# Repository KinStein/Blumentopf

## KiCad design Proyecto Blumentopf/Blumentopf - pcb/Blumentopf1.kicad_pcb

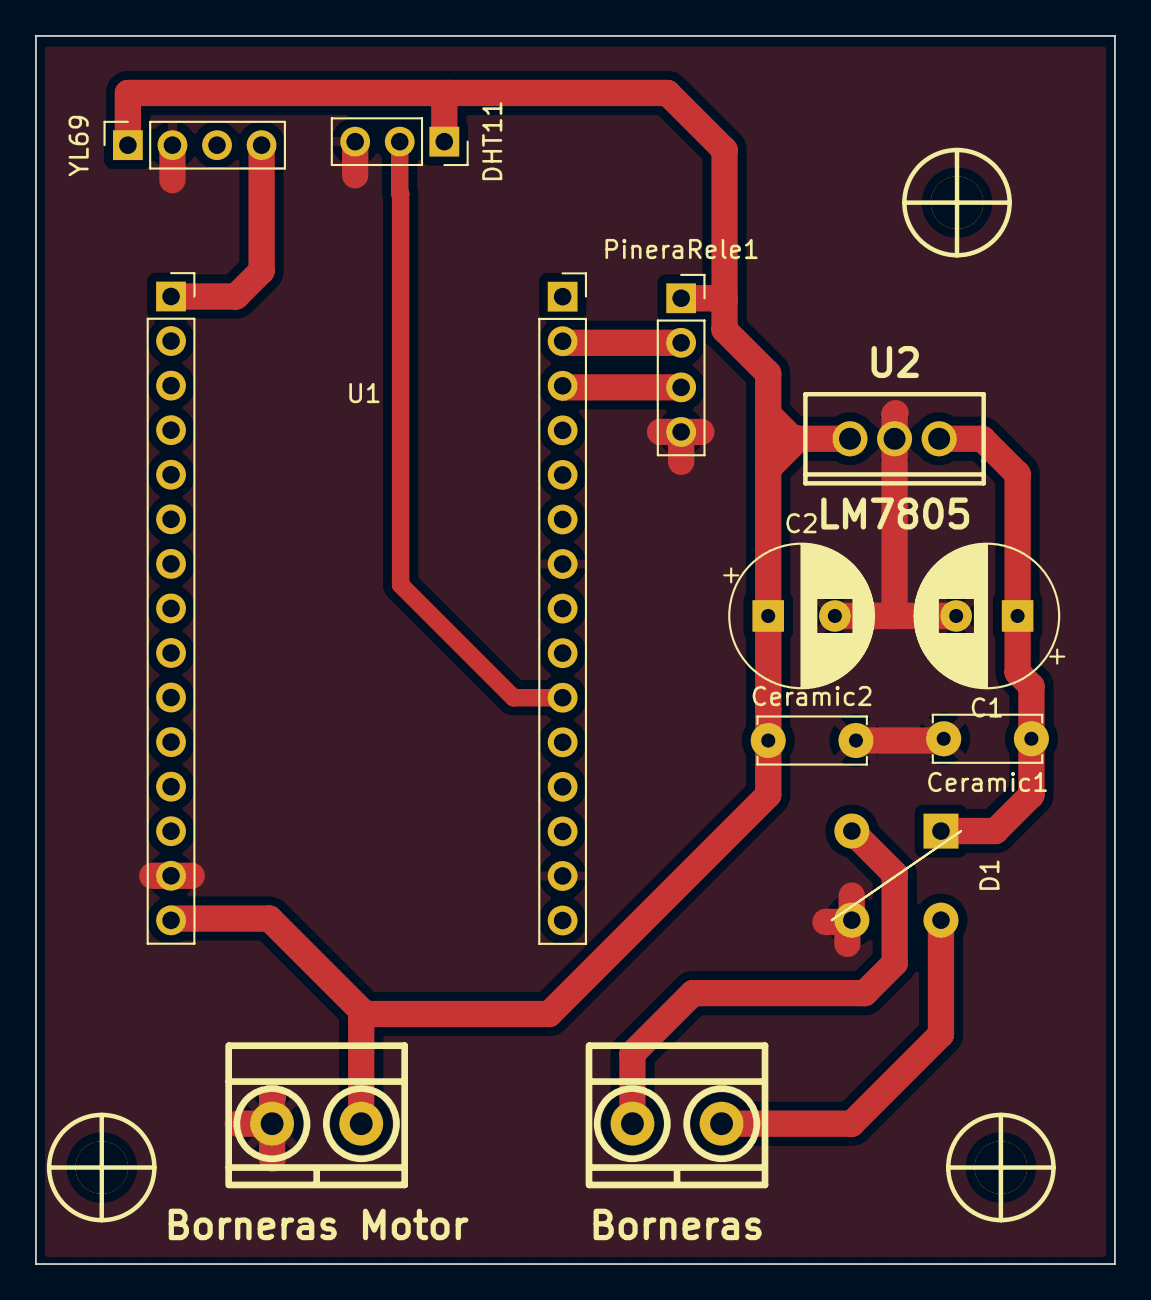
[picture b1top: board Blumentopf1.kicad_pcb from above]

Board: 2 copper layers, 61.5 x 70.0 mm, 15 parts (0 on the bottom side), 9 nets.

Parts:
Agujeros_de_Sujecion1, Agujeros_de_Sujecion3, Agujeros_de_Sujecion4: Mounting_Hole; Separador_M3_10mm
C1: 220u; CP_Radial_D8.0mm_P3.50mm
C2: 100u; CP_Radial_D8.0mm_P3.80mm
Ceramic1, Ceramic2: 100n; C_Disc_D6.0mm_W2.5mm_P5.00mm
D1: Puente de Diodos; Diode_Bridge_Round_D8.9mm
DHT11: Conn_01X03; PinSocket_1x03_P2.54mm_Vertical
J1: Borneras; BORNERA2_AZUL
J2: Borneras Motor; BORNERA2_AZUL
PineraRele1: PineraRele; PinSocket_1x04_P2.54mm_Vertical
U1: ESP8266; ESP6822
U2: LM7805; TO-220
YL69: YL69; PinSocket_1x04_P2.54mm_Vertical

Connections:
+5V: C2.1, Ceramic2.2, DHT11.1, J2.2, PineraRele1.1, U1.15 (VIN), U2.3 (VO), YL69.1
A0: U1.1 (A0), YL69.4
GND: C1.2, C2.2, Ceramic1.2, Ceramic2.2, D1.3 (-), DHT11.3, J2.1, PineraRele1.4, U1.14 (GND), U1.22 (GND), U1.29 (GND), U2.2 (GND), YL69.2
GPIO4: PineraRele1.3, U1.18 (GPI04)
GPIO5: PineraRele1.2, U1.17 (GPI05)
unnamed: C1.1, Ceramic1.1, D1.1 (+), U2.1 (VI)
unnamed: D1.2, J1.1
unnamed: D1.4, J1.2
unnamed: DHT11.2, U1.25 (GPIO13)
